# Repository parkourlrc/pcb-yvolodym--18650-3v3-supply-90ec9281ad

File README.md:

# 18650-3v3-supply

Stabile 3,3-V-Versorgung aus einer 18650-Li-Ion-Zelle, inklusive USB-Ladung und Zellschutz.
KiCad-Projekt (KiCad 10).

## Blockschaltbild

```mermaid
flowchart LR
    USB["USB-C 5 V<br/>(P1)"] -->|VBUS| CHG["TP4056 (U1)<br/>Laden 0,9 A"]
    CHG -->|BAT+| BAT["18650 (BT1)<br/>+ DW01A / FS8205A<br/>Schutz"]
    BAT -->|BAT+| BOOST["MT3608 (U3)<br/>Boost 4,0 V<br/>über SS14"]
    BOOST -->|VBOOST| LDO["AP2112K-3.3 (U4)<br/>LDO"]
    LDO -->|+3V3| OUT["3,3 V<br/>(J1)"]
    BAT -->|"R8/R9 ÷2"| SENSE["VBAT_SENSE<br/>(J1 Pin 3)"]
```

1. **Laden** – USB-C-Buchse (P1, 5 V) → TP4056 (U1), Ladestrom ca. 0,9 A (R1 = 1,2 kΩ an PROG,
   laut Datenblatt-Tabelle; für 1 A: R1 = 1,1 kΩ). CC1/CC2 je 5,1 kΩ (R10/R11) nach GND, damit
   USB-C-Netzteile 5 V liefern.
   LEDs: D1 rot = lädt, D2 grün = voll. TEMP liegt an GND (NTC-Überwachung deaktiviert).
2. **Akku + Schutz** – 18650-Zelle (BT1), Pluspol über Schalter SW2 an BAT+, Minuspol an BAT−; DW01A (U5) + Dual-MOSFET FS8205A (Q1).
   Abschaltung bei Überladung 4,3 V / Tiefentladung 2,4 V / Überstrom.
   Systemmasse GND = P− (hinter dem FS8205A).
3. **Boost** – MT3608 (U3) mit L1 = 22 µH (≥ 2 A) und Schottky D3 (SS14) auf ca. 4,0 V (Netz `VBOOST`):
   `Vout = 0,6 V × (1 + R6/R7) = 0,6 × (1 + 22k/3,9k) ≈ 3,98 V`.
   Für 5 V Ausgang: R7 = 3 kΩ. Bei vollem Akku (4,2 V) taktet der Boost nur noch wenig (4,2 V − U_F(SS14) < 3,98 V), der LDO regelt.
4. **LDO** – AP2112K-3.3 (U4) aus `VBOOST` → stabile 3,3 V an J1 (Eingangsbereich Akku 2,4 … 4,2 V, untere Grenze = DW01A-Abschaltung).

**VBAT_SENSE:** Akkuspannung / 2 über Teiler R8/R9 (2 × 100 kΩ) für einen ADC.
Bei ca. 1,5 V (= 3,0 V Akku) sollte der Verbraucher in den Schlafmodus gehen.

## Anschlüsse

| Ref | Funktion | Pins |
|-----|----------|------|
| P1  | USB_5V_IN | USB-C-Buchse (GCT USB4105), nur VBUS/GND/CC1/CC2 genutzt |
| J1  | OUT_3V3   | 3-polig JST-EH (1 = +3V3, 2 = GND, 3 = VBAT_SENSE) |

## Stückliste (Hauptbauteile)

| Ref | Wert |
|-----|------|
| U1 | TP4056 Lade-IC |
| U5 | DW01A Akkuschutz |
| Q1 | FS8205A Dual-N-MOSFET |
| U3 | MT3608 Boost-Wandler |
| U4 | AP2112K-3.3 LDO |
| BT1 | 18650 Li-Ion |
| L1 | 22 µH / ≥ 2 A |
| D1, D2 | LED rot / grün |
| D3 | SS14 Schottky |
| SW2 | Schiebeschalter SPDT (XKB DMx), trennt Zelle (BT1+) von BAT+ |
| C1, C2 | 10 µF (VBUS bzw. BAT+ am TP4056) |
| C3 | 100 nF (VCC DW01A) |
| C5 | 22 µF (VBOOST, Ausgang MT3608) |
| C6 | 22 µF (BAT+, Eingang MT3608) |
| C7 | 1 µF (VBOOST, Eingang LDO) |
| C8 | 10 µF (+3V3, Ausgang LDO) |
| R1–R11 | 1,2k, 1k, 1k, 100R, 1k, 22k, 3,9k, 100k, 100k, 5,1k, 5,1k |
| P1 | USB-C-Buchse GCT USB4105 |
| J1 | JST EH 3-polig |

## Dateien

| Datei | Inhalt |
|-------|--------|
| `Akku_3V3_Versorgung.kicad_pro` | KiCad-Projekt |
| `Akku_3V3_Versorgung.kicad_sch` | Schaltplan |
| `Akku_3V3_Versorgung.kicad_pcb` | Platine (Bauteile platziert, nicht geroutet) |
| `Akku_3V3_Versorgung.kicad_dru` | Eigene Design-Regeln für den DRC |
| `Akku3V3.kicad_sym` | Projektlokale Symbolbibliothek |
| `sym-lib-table` | Bindet `Akku3V3` über `${KIPRJMOD}` ein |
| `voltage-measurements.md` | Soll- und Messwerte der Spannungen |
| `doc/` | Datenblätter der ICs (TP4056, DW01A, FS8205A, MT3608, AP2112) |

## Status

- [x] Schaltplan
- [x] Footprints zuweisen
- [x] Bauteile platziert
- [ ] Routing
- [ ] Fertigungsdaten (Gerber/Bohrdaten werden nicht eingecheckt, siehe `.gitignore`)

## Lizenz

Copyright © 2026 Eugen Vladimirski

Dieses Projekt steht unter der **CERN Open Hardware Licence Version 2 – Strongly Reciprocal**
(SPDX: `CERN-OHL-S-2.0`), siehe [`LICENSE`](LICENSE).

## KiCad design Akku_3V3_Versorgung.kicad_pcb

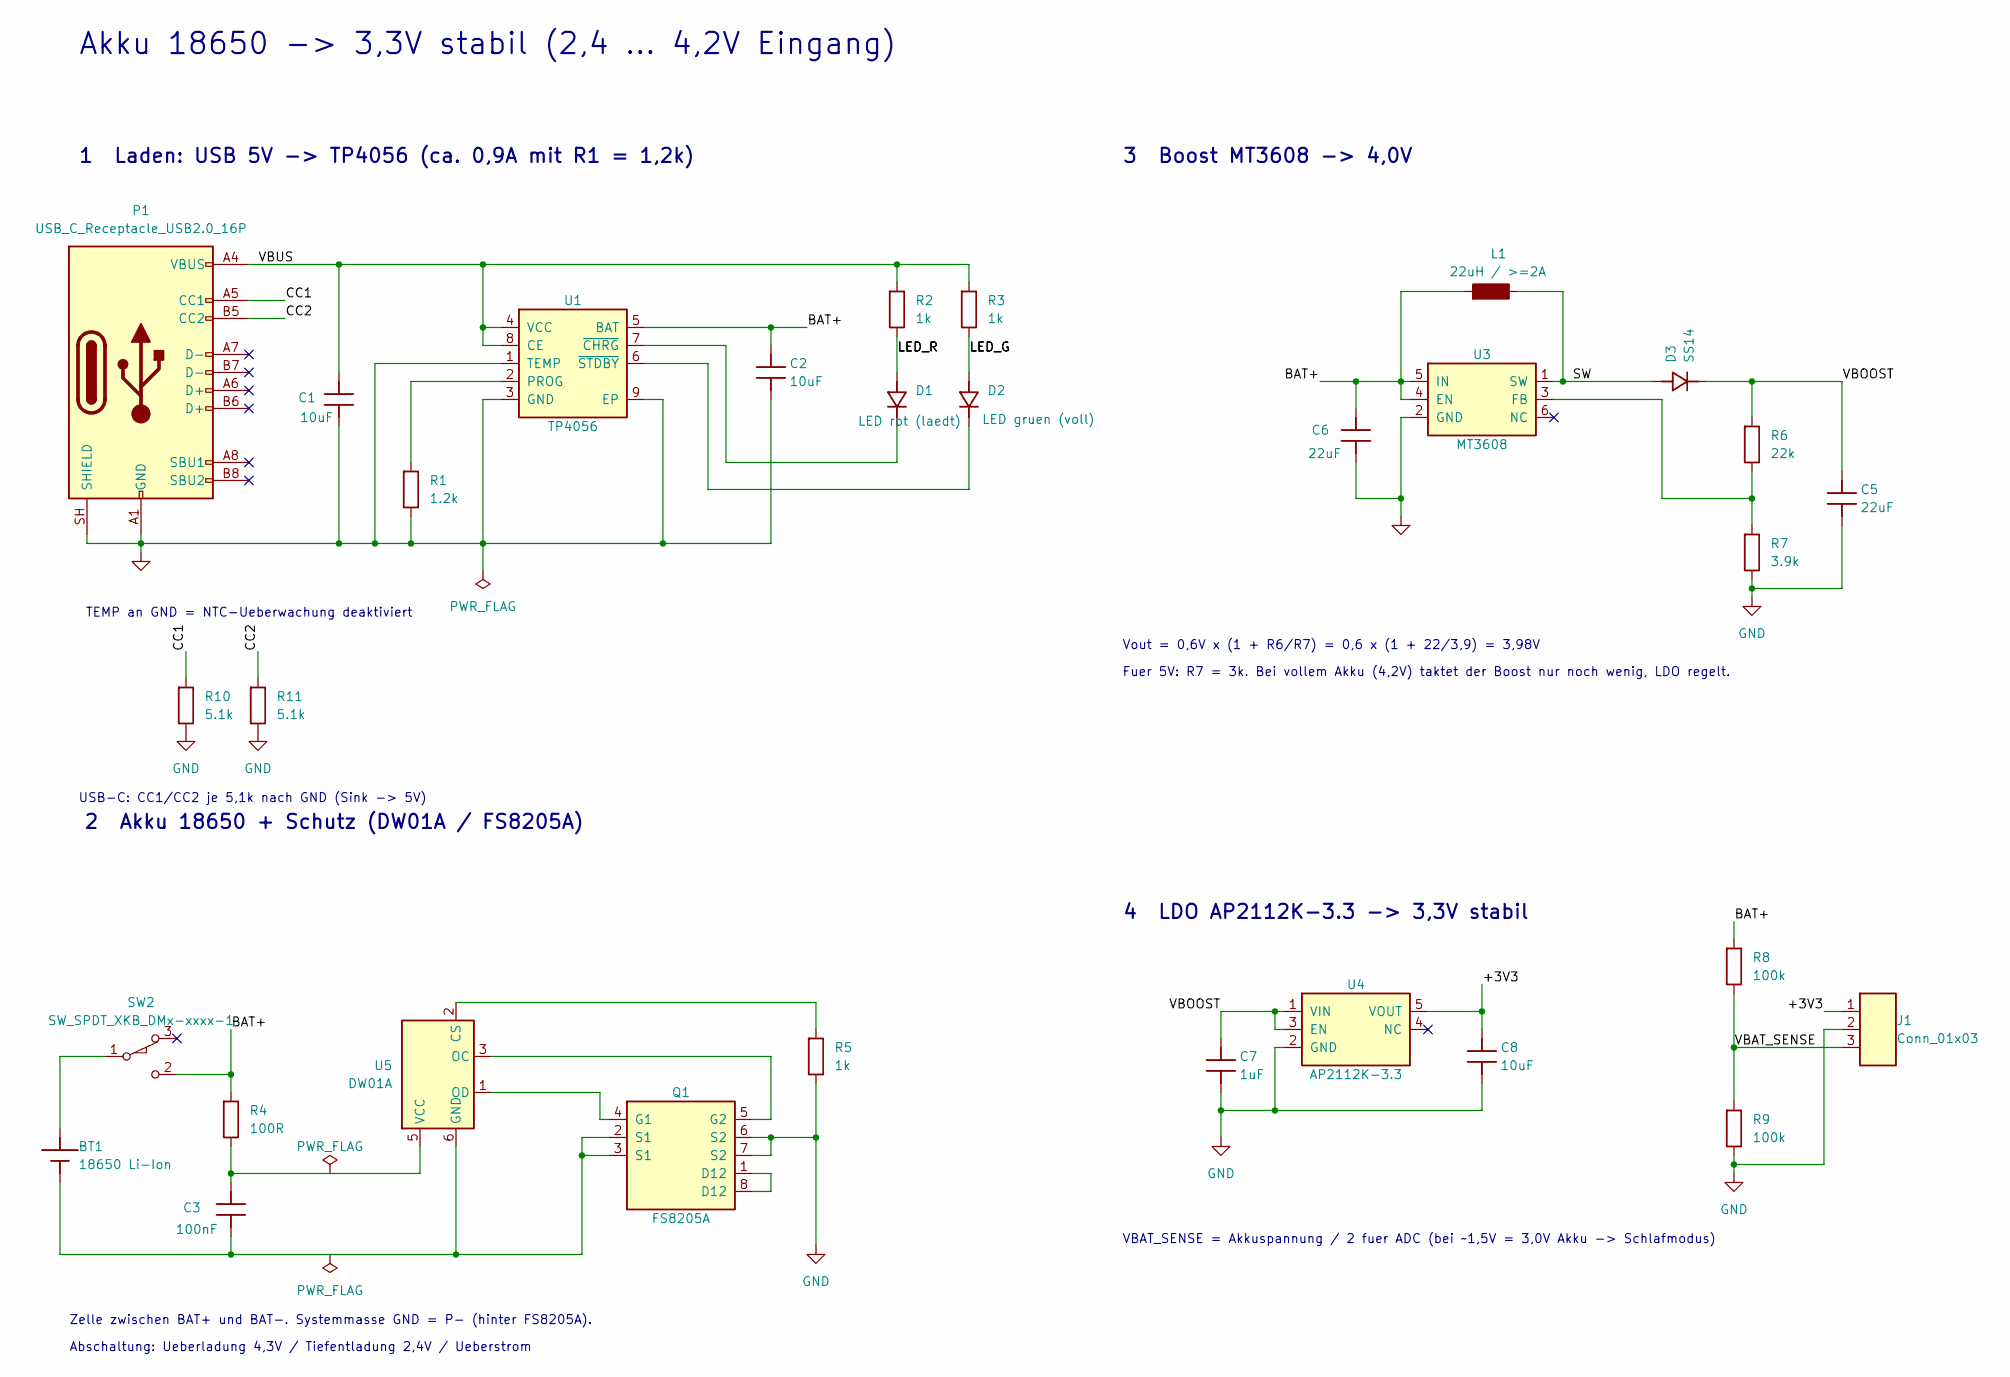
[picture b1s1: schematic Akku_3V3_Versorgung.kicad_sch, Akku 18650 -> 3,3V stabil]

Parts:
BT1: 18650 Li-Ion; NCR18650B
C1, C2, C8: 10uF; C_1206_3216Metric
C3: 100nF; C_1206_3216Metric
C5, C6: 22uF; C_1206_3216Metric
C7: 1uF; C_1206_3216Metric
D1: LED rot (laedt); LED_D2.0mm_W4.8mm_H2.5mm_FlatTop
D2: LED gruen (voll); LED_D2.0mm_W4.8mm_H2.5mm_FlatTop
D3: SS14; D_SMA
J1: Conn_01x03; JST_EH_B3B-EH-A_1x03_P2.50mm_Vertical
L1: 22uH / >=2A; L_1206_3216Metric
P1: USB_C_Receptacle_USB2.0_16P; USB_C_Receptacle_GCT_USB4105-xx-A_16P_TopMnt_Horizontal
Q1: FS8205A; TSSOP-8_4.4x3mm_P0.65mm
R1: 1.2k; R_1206_3216Metric
R2, R3, R5: 1k; R_1206_3216Metric
R4: 100R; R_1206_3216Metric
R6: 22k; R_1206_3216Metric
R7: 3.9k; R_1206_3216Metric
R8, R9: 100k; R_1206_3216Metric
R10, R11: 5.1k; R_1206_3216Metric
SW2: SW_SPDT_XKB_DMx-xxxx-1; Switch_Small
U1: TP4056; SOIC-8-1EP_3.9x4.9mm_P1.27mm_EP2.29x3mm
U3: MT3608; SOT-23-6
U4: AP2112K-3.3; SOT-23-5
U5: DW01A; SOT-23-6

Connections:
/+3V3: C8.1, J1.1, U4.5 (VOUT)
/BAT+: C2.1, C6.1, L1.1, R4.1, R8.1, SW2.2 (B), U1.5 (BAT), U3.4 (EN), U3.5 (IN)
/CC1: P1.A5 (CC1), R10.1
/CC2: P1.B5 (CC2), R11.1
/LED_G: D2.2 (A), R3.2
/LED_R: D1.2 (A), R2.2
/SW: D3.2 (A), L1.2, U3.1 (SW)
/VBAT_SENSE: J1.3, R8.2, R9.1
/VBOOST: C5.1, C7.1, D3.1 (K), R6.1, U4.1 (VIN), U4.3 (EN)
/VBUS: C1.1, P1.A4 (VBUS), P1.A9 (VBUS), P1.B4 (VBUS), P1.B9 (VBUS), R2.1, R3.1, U1.4 (VCC), U1.8 (CE)
GND: C1.2, C2.2, C5.2, C6.2, C7.2, C8.2, J1.2, P1.A1 (GND), P1.A12 (GND), P1.B1 (GND), P1.B12 (GND), P1.SH (SHIELD), Q1.6 (S2), Q1.7 (S2), R1.2, R5.2, R7.2, R9.2, R10.2, R11.2, U1.1 (TEMP), U1.3 (GND), U1.9 (EP), U3.2 (GND), U4.2 (GND)
unnamed: BT1.1 (+), SW2.1 (A)
unnamed: BT1.2 (-), C3.2, Q1.2 (S1), Q1.3 (S1), U5.6 (GND)
unnamed: D1.1 (K), U1.7 (~CHRG)
unnamed: D2.1 (K), U1.6 (~STDBY)
unnamed: Q1.1 (D12), Q1.8 (D12)
unnamed: Q1.4 (G1), U5.1 (OD)
unnamed: Q1.5 (G2), U5.3 (OC)
unnamed: R1.1, U1.2 (PROG)
unnamed: R6.2, R7.1, U3.3 (FB)
unnamed: R5.1, U5.2 (CS)
unnamed: C3.1, R4.2, U5.5 (VCC)

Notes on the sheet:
1 Laden: USB 5V -> TP4056 (ca. 0,9A mit R1 = 1,2k)
Akku 18650 -> 3,3V stabil (2,4 ... 4,2V Eingang)
VBAT_SENSE = Akkuspannung / 2 fuer ADC (bei ~1,5V = 3,0V Akku -> Schlafmodus)
Fuer 5V: R7 = 3k. Bei vollem Akku (4,2V) taktet der Boost nur noch wenig, LDO regelt.
3 Boost MT3608 -> 4,0V
Vout = 0,6V x (1 + R6/R7) = 0,6 x (1 + 22/3,9) = 3,98V
Abschaltung: Ueberladung 4,3V / Tiefentladung 2,4V / Ueberstrom
4 LDO AP2112K-3.3 -> 3,3V stabil
Zelle zwischen BAT+ und BAT-. Systemmasse GND = P- (hinter FS8205A).
USB-C: CC1/CC2 je 5,1k nach GND (Sink -> 5V)
2 Akku 18650 + Schutz (DW01A / FS8205A)
TEMP an GND = NTC-Ueberwachung deaktiviert

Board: 2 copper layers, 31 parts (6 on the bottom side), 22 nets, no tracks yet.
